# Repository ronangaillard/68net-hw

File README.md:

# 68net

A SCSI to ethernet board

[My blog post](https://ronangaillard.github.io/posts/68net-a-modern-scsi2ethernet-board-part1/) for more background info 

## Contributing

To make sure Kicad and git work fluently run the following before commiting :

```bash
git config --global filter.kicad_project.clean "sed -E 's/^update=.*$/update=Date/'"
git config --global filter.kicad_project.smudge cat
git config --global filter.kicad_sch.clean "sed -E 's/#(PWR|FLG)[0-9]+/#\1?/'"
git config --global filter.kicad_sch.smudge cat
```

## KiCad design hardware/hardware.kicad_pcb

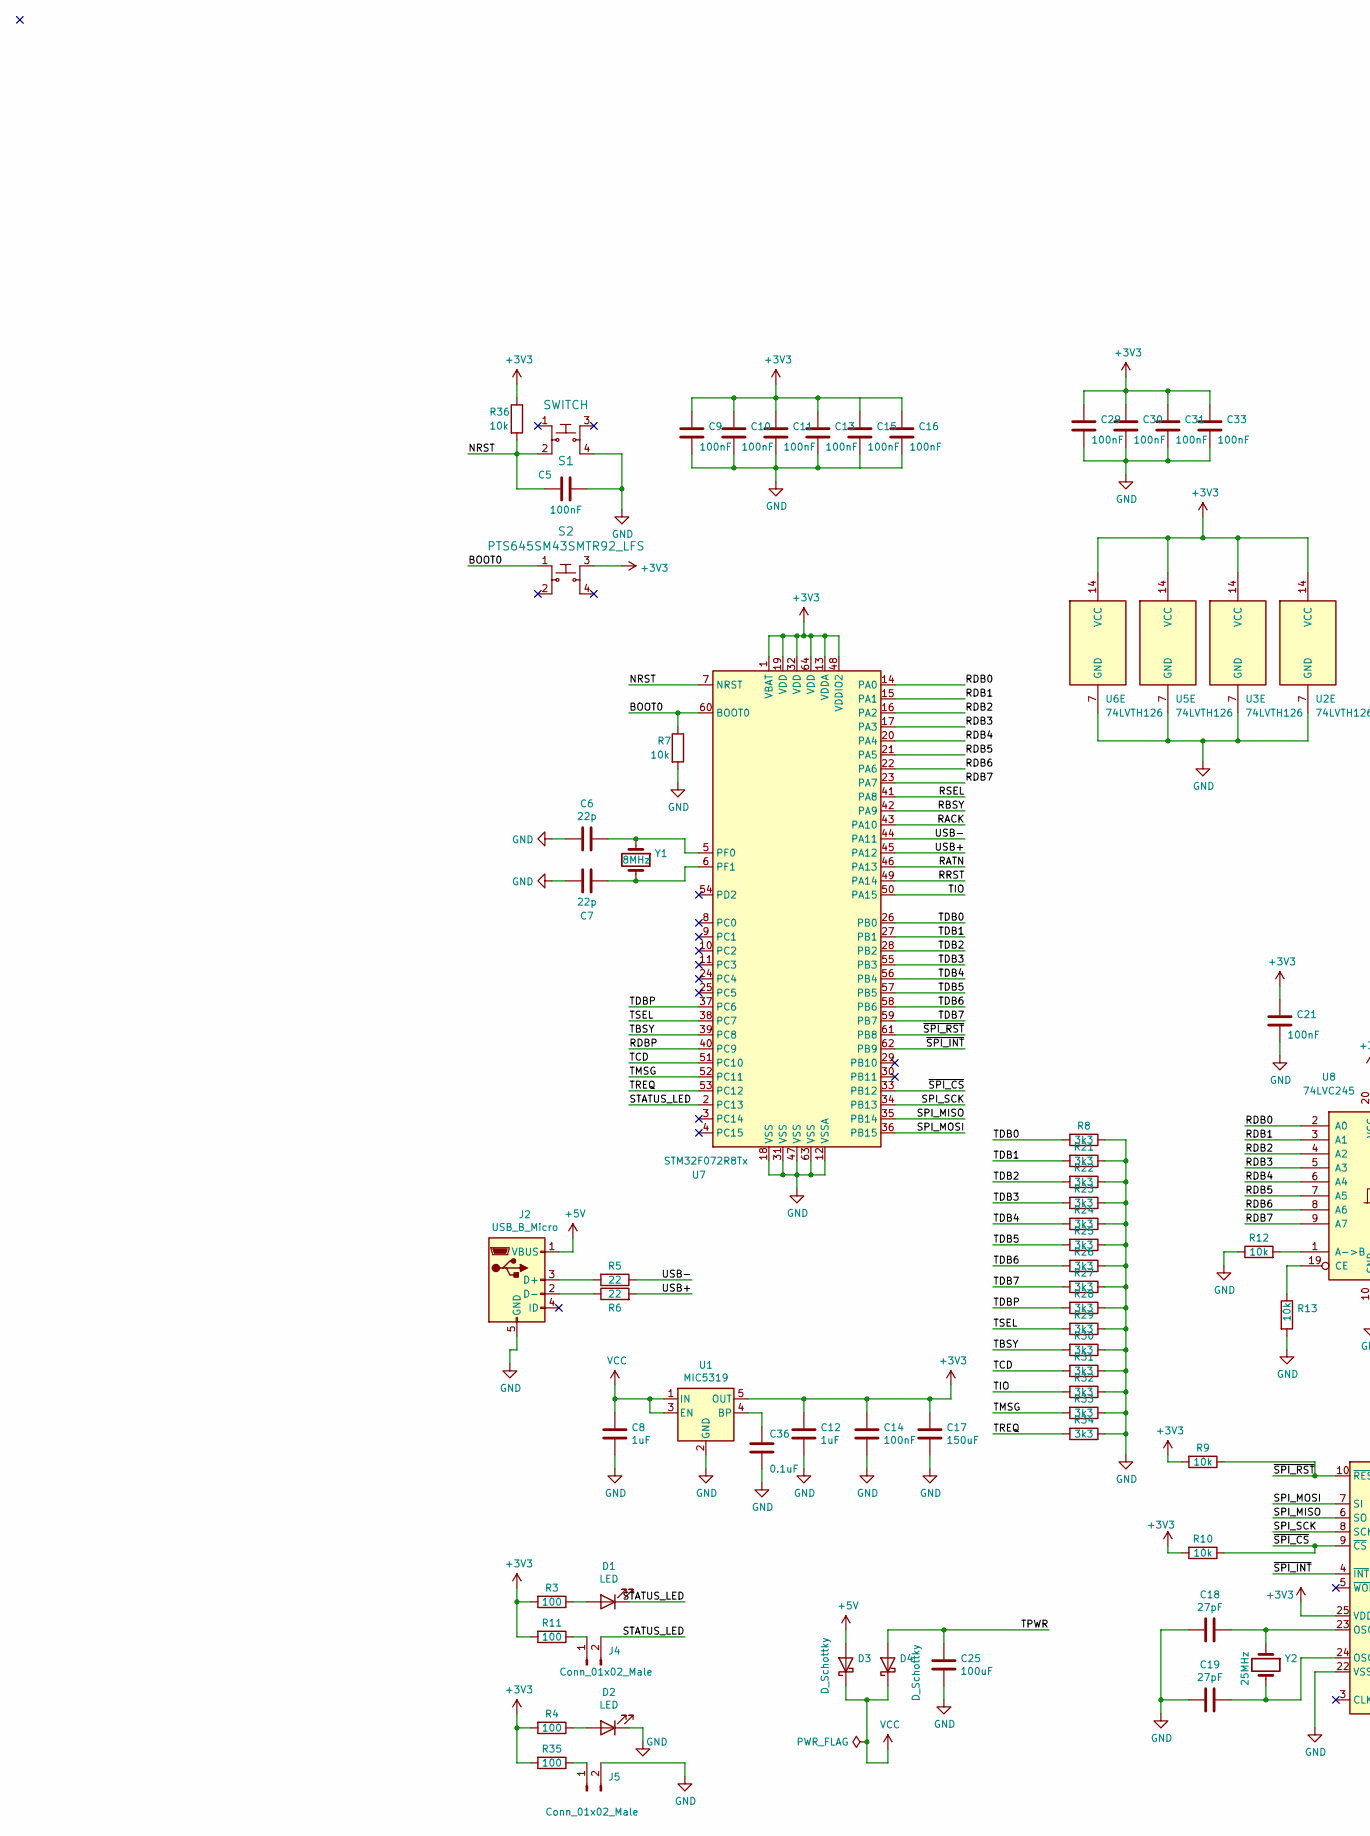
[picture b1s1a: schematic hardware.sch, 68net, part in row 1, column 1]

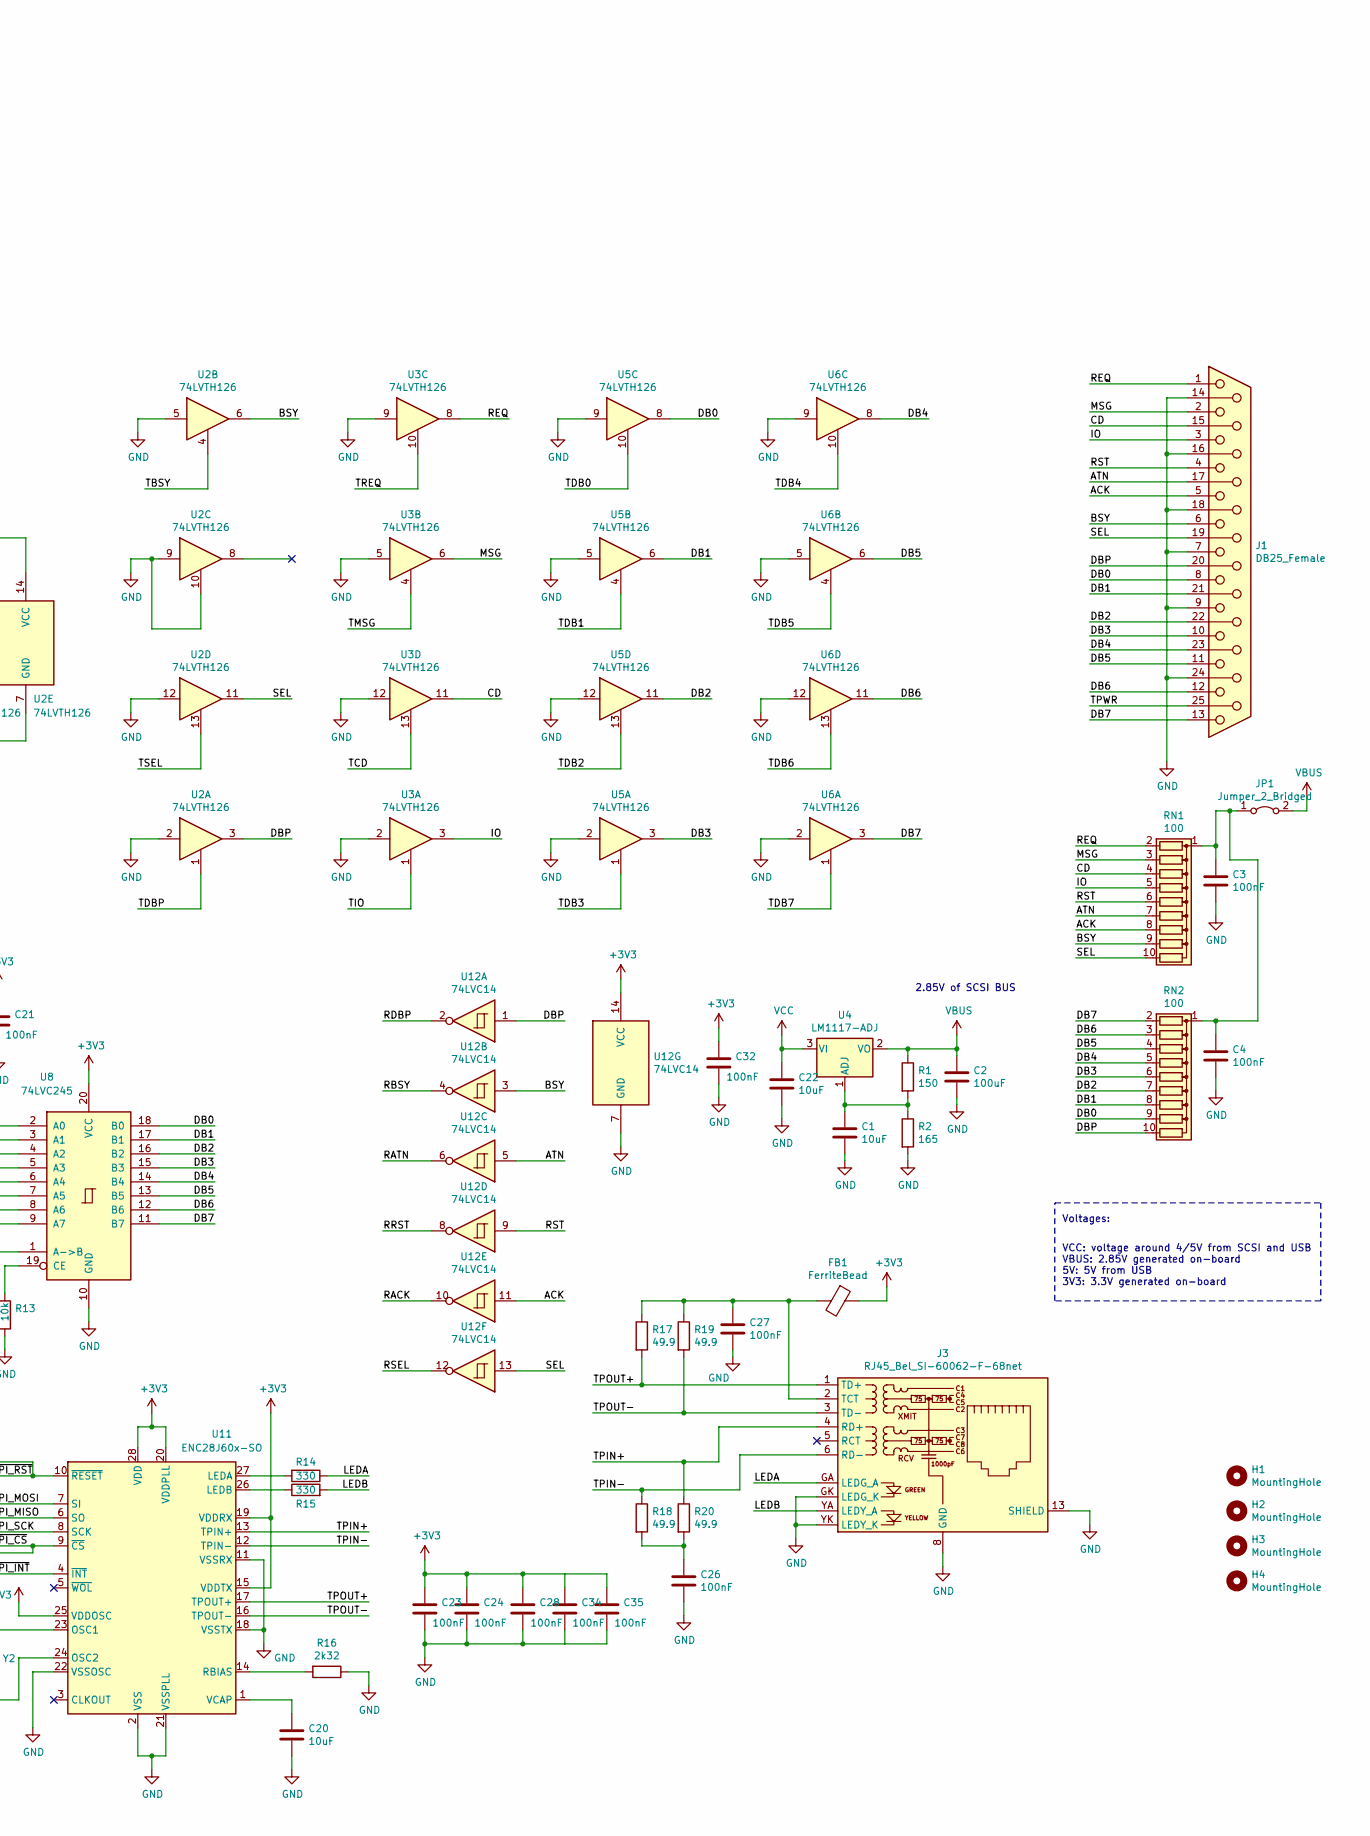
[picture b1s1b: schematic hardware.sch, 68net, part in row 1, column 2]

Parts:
C1, C20, C22: 10uF; C_1206_3216Metric_Pad1.42x1.75mm_HandSolder; Digi-Key_PN 1276-1079-1-ND
C2: 100uF; C_1206_3216Metric_Pad1.42x1.75mm_HandSolder; Digi-Key_PN 1276-1782-1-ND
C3, C4, C5, C9, C10, C11, C13, C14, C15, C16, C21, C23, C24, C26, C27, C28, C29, C30, C31, C32, C33, C34, C35: 100nF; C_1206_3216Metric_Pad1.42x1.75mm_HandSolder; Digi-Key_PN 1276-1017-1-ND
C6, C7: 22p; C_1206_3216Metric_Pad1.42x1.75mm_HandSolder; Digi-Key_PN 1276-1203-1-ND
C8, C12: 1uF; C_1206_3216Metric_Pad1.42x1.75mm_HandSolder; Digi-Key_PN 1276-3091-1-ND
C17: 150uF; C_1206_3216Metric_Pad1.42x1.75mm_HandSolder; Digi-Key_PN 490-13964-1-ND
C18, C19: 27pF; C_1206_3216Metric_Pad1.42x1.75mm_HandSolder; Digi-Key_PN 1276-2827-1-ND
C25: 100uF; CP_Elec_6.3x5.4; Digi-Key_PN 493-2105-1-ND
C36: 0.1uF; C_1206_3216Metric_Pad1.42x1.75mm_HandSolder; Digi-Key_PN CL31B104KBCNNNC
D1, D2: LED; LED_1206_3216Metric_Pad1.42x1.75mm_HandSolder; Digi-Key_PN 60-1456-1-ND
D3, D4: D_Schottky; D_SOD-523; Digi-Key_PN RB521S30T1GOSCT-ND
FB1: FerriteBead; L_0603_1608Metric_Pad1.05x0.95mm_HandSolder; Digi-Key_PN 445-8694-1-ND
H1, H2, H3, H4: MountingHole; MountingHole_3.2mm_M3_Pad
J1: DB25_Female; DSUB-25_Female_Horizontal_Double; Digi-Key_PN 609-1507-ND
J2: USB_B_Micro; TE_2172034-1; Digi-Key_PN 135698-ND
J3: RJ45_Bel_SI-60062-F-68net; SI-60062-F; Digi-Key_PN 380-1106-ND
J4, J5: Conn_01x02_Male; PinHeader_1x02_P2.54mm_Vertical
JP1: Jumper_2_Bridged; PinHeader_1x02_P2.54mm_Vertical
R1: 150; R_0805_2012Metric_Pad1.15x1.40mm_HandSolder; Digi-Key_PN RMCF0805FT150RCT-ND
R2: 165; R_0805_2012Metric_Pad1.15x1.40mm_HandSolder; Digi-Key_PN RMCF0805FT165RCT-ND
R3, R4, R11, R35: 100; R_0805_2012Metric_Pad1.15x1.40mm_HandSolder; Digi-Key_PN RMCF0805FT165RCT-ND
R5, R6: 22; R_0805_2012Metric_Pad1.15x1.40mm_HandSolder; Digi-Key_PN RMCF0603FT22R0CT-ND
R7, R9, R10, R36: 10k; R_0805_2012Metric_Pad1.15x1.40mm_HandSolder; Digi-Key_PN RMCF0603JT10K0CT-ND
R8, R21, R22, R23, R24, R25, R26, R27, R28, R29, R30, R31, R32, R33, R34: 3k3; R_0805_2012Metric_Pad1.15x1.40mm_HandSolder
R12, R13: 10k; R_0805_2012Metric_Pad1.15x1.40mm_HandSolder
R14, R15: 330; R_0805_2012Metric_Pad1.15x1.40mm_HandSolder; Digi-Key_PN RMCF0805JT330RCT-ND
R16: 2k32; R_0805_2012Metric_Pad1.15x1.40mm_HandSolder; Digi-Key_PN RNCF0603DTE2K32CT-ND
R17, R18, R19, R20: 49.9; R_0805_2012Metric_Pad1.15x1.40mm_HandSolder; Digi-Key_PN RNCP0603FTD49R9CT
RN1, RN2: 100; R_Array_SIP10; Digi-Key_PN 4610X-1-101LF-ND
S1: SWITCH; Switch_Tactile_SMD_6x6mm; Digi-Key_PN TL3301AF160QG
S2: PTS645SM43SMTR92_LFS; Switch_Tactile_SMD_6x6mm; Digi-Key_PN TL3301AF160QG
U1: MIC5319; SOT-23-5_HandSoldering; Digi-Key_PN MIC5319-3.3YD5-TR
U2, U3, U5, U6: 74LVTH126; SOIC-14_3.9x8.7mm_P1.27mm; Digi-Key_PN 296-8663-1-ND
U4: LM1117-ADJ; SOT-223; Digi-Key_PN LM1117MPX-ADJ/NOPBCT-ND
U7: STM32F072R8Tx; LQFP-64_10x10mm_P0.5mm; Digi-Key_PN 497-17362-1-ND
U8: 74LVC245; SOIC-20W_7.5x12.8mm_P1.27mm; Digi-Key_PN 296-1232-1-ND
U11: ENC28J60x-SO; SOIC-28W_7.5x17.9mm_P1.27mm; Digi-Key_PN ENC28J60-I/SO-ND
U12: 74LVC14; SOIC-14_3.9x8.7mm_P1.27mm; Digi-Key_PN 296-1699-1-ND
Y1: 8MHz; Crystal_HC49-4H_Vertical; Digi-Key_PN 887-1253-ND
Y2: 25MHz; Crystal_HC49-4H_Vertical; Digi-Key_PN 887-1233-ND

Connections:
+3V3: C9.1, C10.1, C11.1, C12.1, C13.1, C14.1, C15.1, C16.1, C17.1, C21.1, C23.1, C24.1, C28.1, C29.1, C30.1, C31.1, C32.1, C33.1, C34.1, C35.1, FB1.1, R3.2, R4.2, R9.2, R10.2, R11.2, R35.2, R36.1, S2.3, U1.5 (OUT), U2.14 (VCC), U3.14 (VCC), U5.14 (VCC), U6.14 (VCC), U7.1 (VBAT), U7.13 (VDDA), U7.19 (VDD), U7.32 (VDD), U7.48 (VDDIO2), U7.64 (VDD), U8.20 (VCC), U11.15 (VDDTX), U11.19 (VDDRX), U11.20 (VDDPLL), U11.25 (VDDOSC), U11.28 (VDD), U12.14 (VCC)
+5V: D3.2 (A), J2.1 (VBUS)
/ACK: J1.5, RN1.8 (R7), U12.11
/ATN: J1.17, RN1.7 (R6), U12.5
/BOOT0: R7.1, S2.1, U7.60 (BOOT0)
/BSY: J1.6, RN1.9 (R8), U2.6, U12.3
/CD: J1.15, RN1.4 (R3), U3.11
/DB0: J1.8, RN2.9 (R8), U5.8, U8.18 (B0)
/DB1: J1.21, RN2.8 (R7), U5.6, U8.17 (B1)
/DB2: J1.22, RN2.7 (R6), U5.11, U8.16 (B2)
/DB3: J1.10, RN2.6 (R5), U5.3, U8.15 (B3)
/DB4: J1.23, RN2.5 (R4), U6.8, U8.14 (B4)
/DB5: J1.11, RN2.4 (R3), U6.6, U8.13 (B5)
/DB6: J1.12, RN2.3 (R2), U6.11, U8.12 (B6)
/DB7: J1.13, RN2.2 (R1), U6.3, U8.11 (B7)
/DBP: J1.20, RN2.10 (R9), U2.3, U12.1
/IO: J1.3, RN1.5 (R4), U3.3
/LEDA: J3.GA (LEDG_A), R14.1
/LEDB: J3.YA (LEDY_A), R15.2
/MSG: J1.2, RN1.3 (R2), U3.6
/NRST: C5.2, R36.2, S1.2, U7.7 (NRST)
/RACK: U7.43 (PA10), U12.10
/RATN: U7.46 (PA13), U12.6
/RBSY: U7.42 (PA9), U12.4
/RDB0: U7.14 (PA0), U8.2 (A0)
/RDB1: U7.15 (PA1), U8.3 (A1)
/RDB2: U7.16 (PA2), U8.4 (A2)
/RDB3: U7.17 (PA3), U8.5 (A3)
/RDB4: U7.20 (PA4), U8.6 (A4)
/RDB5: U7.21 (PA5), U8.7 (A5)
/RDB6: U7.22 (PA6), U8.8 (A6)
/RDB7: U7.23 (PA7), U8.9 (A7)
/RDBP: U7.40 (PC9), U12.2
/REQ: J1.1, RN1.2 (R1), U3.8
/RRST: U7.49 (PA14), U12.8
/RSEL: U7.41 (PA8), U12.12
/RST: J1.4, RN1.6 (R5), U12.9
/SEL: J1.19, RN1.10 (R9), U2.11, U12.13
/SPI_MISO: U7.35 (PB14), U11.6 (SO)
/SPI_MOSI: U7.36 (PB15), U11.7 (SI)
/SPI_SCK: U7.34 (PB13), U11.8 (SCK)
/STATUS_LED: D1.1 (K), J4.2, U7.2 (PC13)
/TBSY: R30.2, U2.4, U7.39 (PC8)
/TCD: R31.2, U3.13, U7.51 (PC10)
/TDB0: R8.2, U5.10, U7.26 (PB0)
/TDB1: R21.2, U5.4, U7.27 (PB1)
/TDB2: R22.2, U5.13, U7.28 (PB2)
/TDB3: R23.2, U5.1, U7.55 (PB3)
/TDB4: R24.2, U6.10, U7.56 (PB4)
/TDB5: R25.2, U6.4, U7.57 (PB5)
/TDB6: R26.2, U6.13, U7.58 (PB6)
/TDB7: R27.2, U6.1, U7.59 (PB7)
/TDBP: R28.2, U2.1, U7.37 (PC6)
/TIO: R32.2, U3.1, U7.50 (PA15)
/TMSG: R33.2, U3.4, U7.52 (PC11)
/TPIN+: J3.4 (RD+), R20.1, U11.13 (TPIN+)
/TPIN-: J3.6 (RD-), R18.1, U11.12 (TPIN-)
/TPOUT+: J3.1 (TD+), R17.2, U11.17 (TPOUT+)
/TPOUT-: J3.3 (TD-), R19.2, U11.16 (TPOUT-)
/TPWR: C25.1, D4.2 (A), J1.25
/TREQ: R34.2, U3.10, U7.53 (PC12)
/TSEL: R29.2, U2.13, U7.38 (PC7)
/USB+: R6.2, U7.45 (PA12)
/USB-: R5.1, U7.44 (PA11)
/~SPI_CS~: R10.1, U7.33 (PB12), U11.9 (~CS)
/~SPI_INT~: U7.62 (PB9), U11.4 (~INT)
/~SPI_RST~: R9.1, U7.61 (PB8), U11.10 (~RESET)
GND: C1.2, C2.2, C3.2, C4.2, C5.1, C6.2, C7.2, C8.2, C9.2, C10.2, C11.2, C12.2, C13.2, C14.2, C15.2, C16.2, C17.2, C18.2, C19.2, C20.2, C21.2, C22.2, C23.2, C24.2, C25.2, C26.2, C27.2, C28.2, C29.2, C30.2, C31.2, C32.2, C33.2, C34.2, C35.2, C36.2, D2.1 (K), J1.7, J1.9, J1.14, J1.16, J1.18, J1.24, J2.5 (GND), J3.8 (GND), J3.13 (SHIELD), J3.GK (LEDG_K), J3.YK (LEDY_K), J5.2, R2.2, R7.2, R8.1, R12.1, R13.2, R16.1, R21.1, R22.1, R23.1, R24.1, R25.1, R26.1, R27.1, R28.1, R29.1, R30.1, R31.1, R32.1, R33.1, R34.1, S1.4, U1.2 (GND), U2.2, U2.5, U2.7 (GND), U2.9, U2.10, U2.12, U3.2, U3.5, U3.7 (GND), U3.9, U3.12, U5.2, U5.5, U5.7 (GND), U5.9, U5.12, U6.2, U6.5, U6.7 (GND), U6.9, U6.12, U7.12 (VSSA), U7.18 (VSS), U7.31 (VSS), U7.47 (VSS), U7.63 (VSS), U8.10 (GND), U11.2 (VSS), U11.11 (VSSRX), U11.18 (VSSTX), U11.21 (VSSPLL), U11.22 (VSSOSC), U12.7 (GND)
unnamed: C1.1, R1.2, R2.1, U4.1 (ADJ)
unnamed: C3.1, C4.1, JP1.1 (A), RN1.1 (common), RN2.1 (common)
unnamed: C6.1, U7.5 (PF0), Y1.1
unnamed: C7.1, U7.6 (PF1), Y1.2
unnamed: C18.1, U11.23 (OSC1), Y2.1
unnamed: C19.1, U11.24 (OSC2), Y2.2
unnamed: C20.1, U11.1 (VCAP)
unnamed: C26.1, R18.2, R20.2
unnamed: C27.1, FB1.2, J3.2 (TCT), R17.1, R19.1
unnamed: C36.1, U1.4 (BP)
unnamed: D1.2 (A), R3.1
unnamed: D2.2 (A), R4.1
unnamed: J2.2 (D-), R6.1
unnamed: J2.3 (D+), R5.2
unnamed: J4.1, R11.1
unnamed: J5.1, R35.1
unnamed: R12.2, U8.1 (A->B)
unnamed: R13.1, U8.19 (CE)
unnamed: R14.2, U11.27 (LEDA)
unnamed: R15.1, U11.26 (LEDB)
unnamed: R16.2, U11.14 (RBIAS)
VBUS: C2.1, JP1.2 (B), R1.1, U4.2 (VO)
VCC: C8.1, C22.1, D3.1 (K), D4.1 (K), U1.1 (IN), U1.3 (EN), U4.3 (VI)

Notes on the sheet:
2.85V of SCSI BUS
VCC: voltage around 4/5V from SCSI and USB VBUS: 2.85V generated on-board 5V: 5V from USB 3V3: 3.3V generated on-board
Voltages:

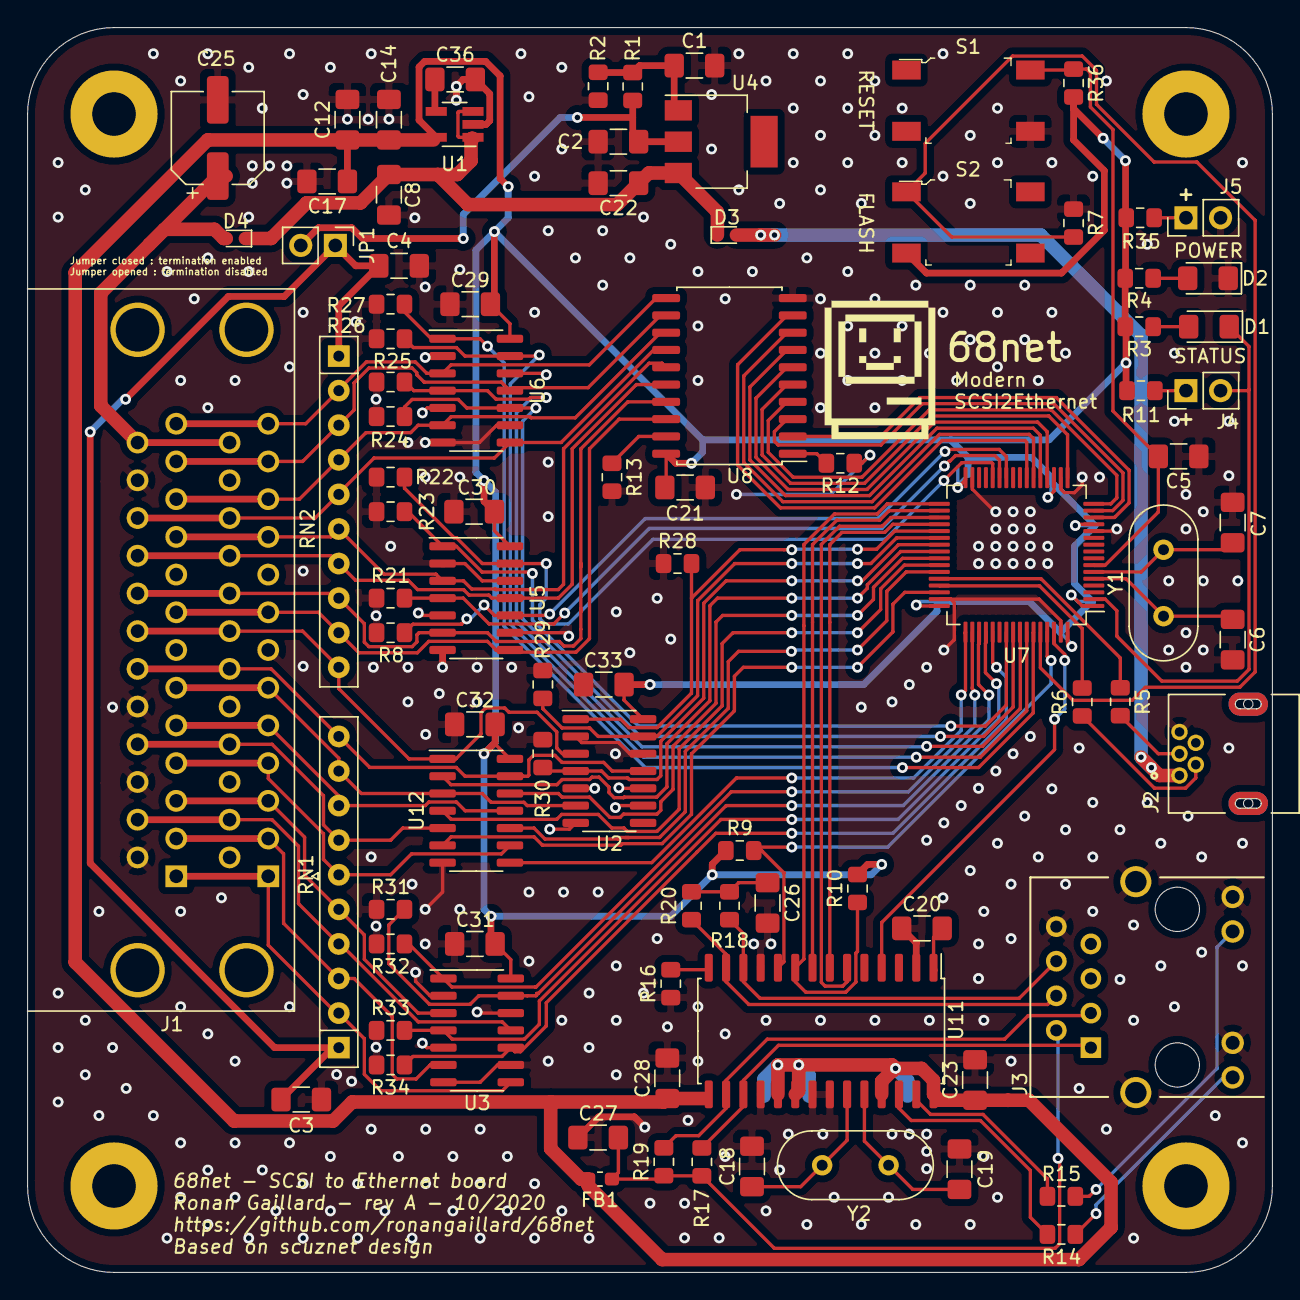
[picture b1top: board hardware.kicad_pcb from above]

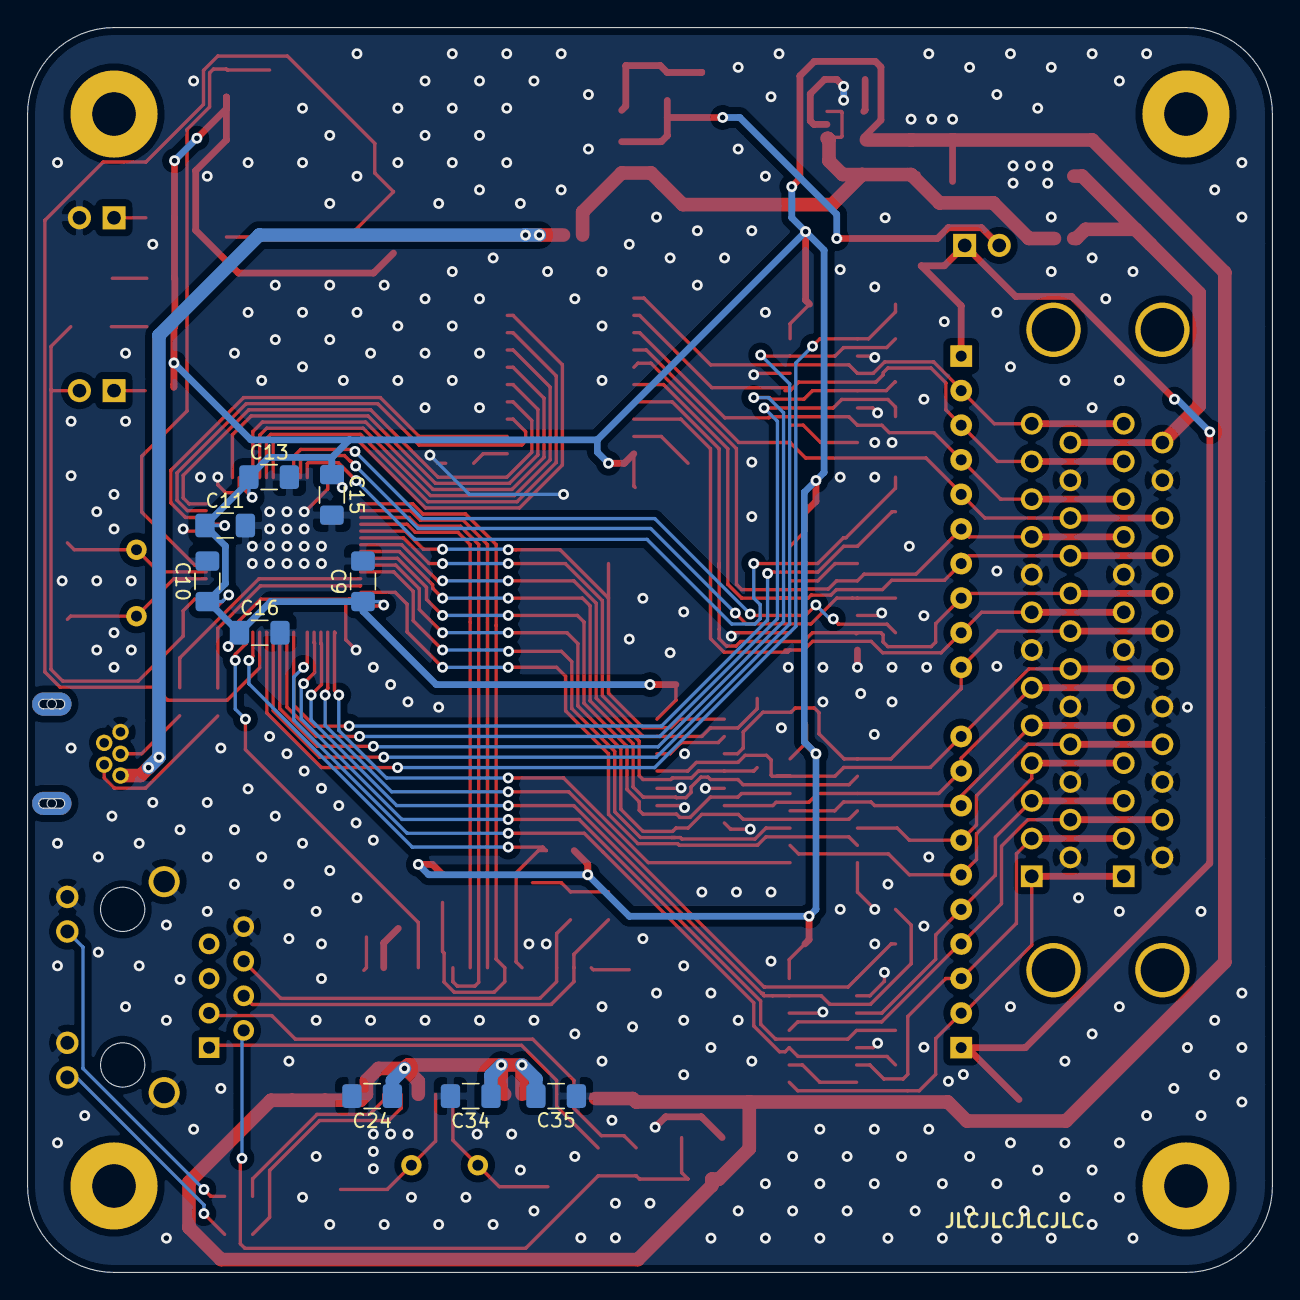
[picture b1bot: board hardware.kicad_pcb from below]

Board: 2 copper layers, 91.4 x 91.4 mm, 103 parts (9 on the bottom side), 91 nets.

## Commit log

2020-11-03 build: add action to plot
2020-11-03 fix: drc and unused pins
2020-11-03 fix: workflow name
2020-11-04 feat: update page settings
2020-11-04 feat: update extension port and place again footprints on pcb
2020-11-04 build: add git things to make diff clearer in the future
2020-11-04 feat: split 15 resistor array into single resistors
2020-11-10 feat: finalize revA-alpha
2020-11-10 doc: update README
2020-11-10 feat: update LDO regulator
2020-11-10 feat: add jumper connector to enable termination
2020-11-10 docs: update readme with badge
2020-11-10 build: generate artifacts only when needed
2020-11-11 feat: add double DB25 connector
2020-11-12 feat: add connectors for external LEDs
2020-11-12 fix: boot and rst signal badly pulled up/down
2020-11-13 fix: wrong pins on LEDs connectors
2020-11-13 feat: add JLCJLC... +fix trace touching usb shield
2020-11-17 feat: update BOM
